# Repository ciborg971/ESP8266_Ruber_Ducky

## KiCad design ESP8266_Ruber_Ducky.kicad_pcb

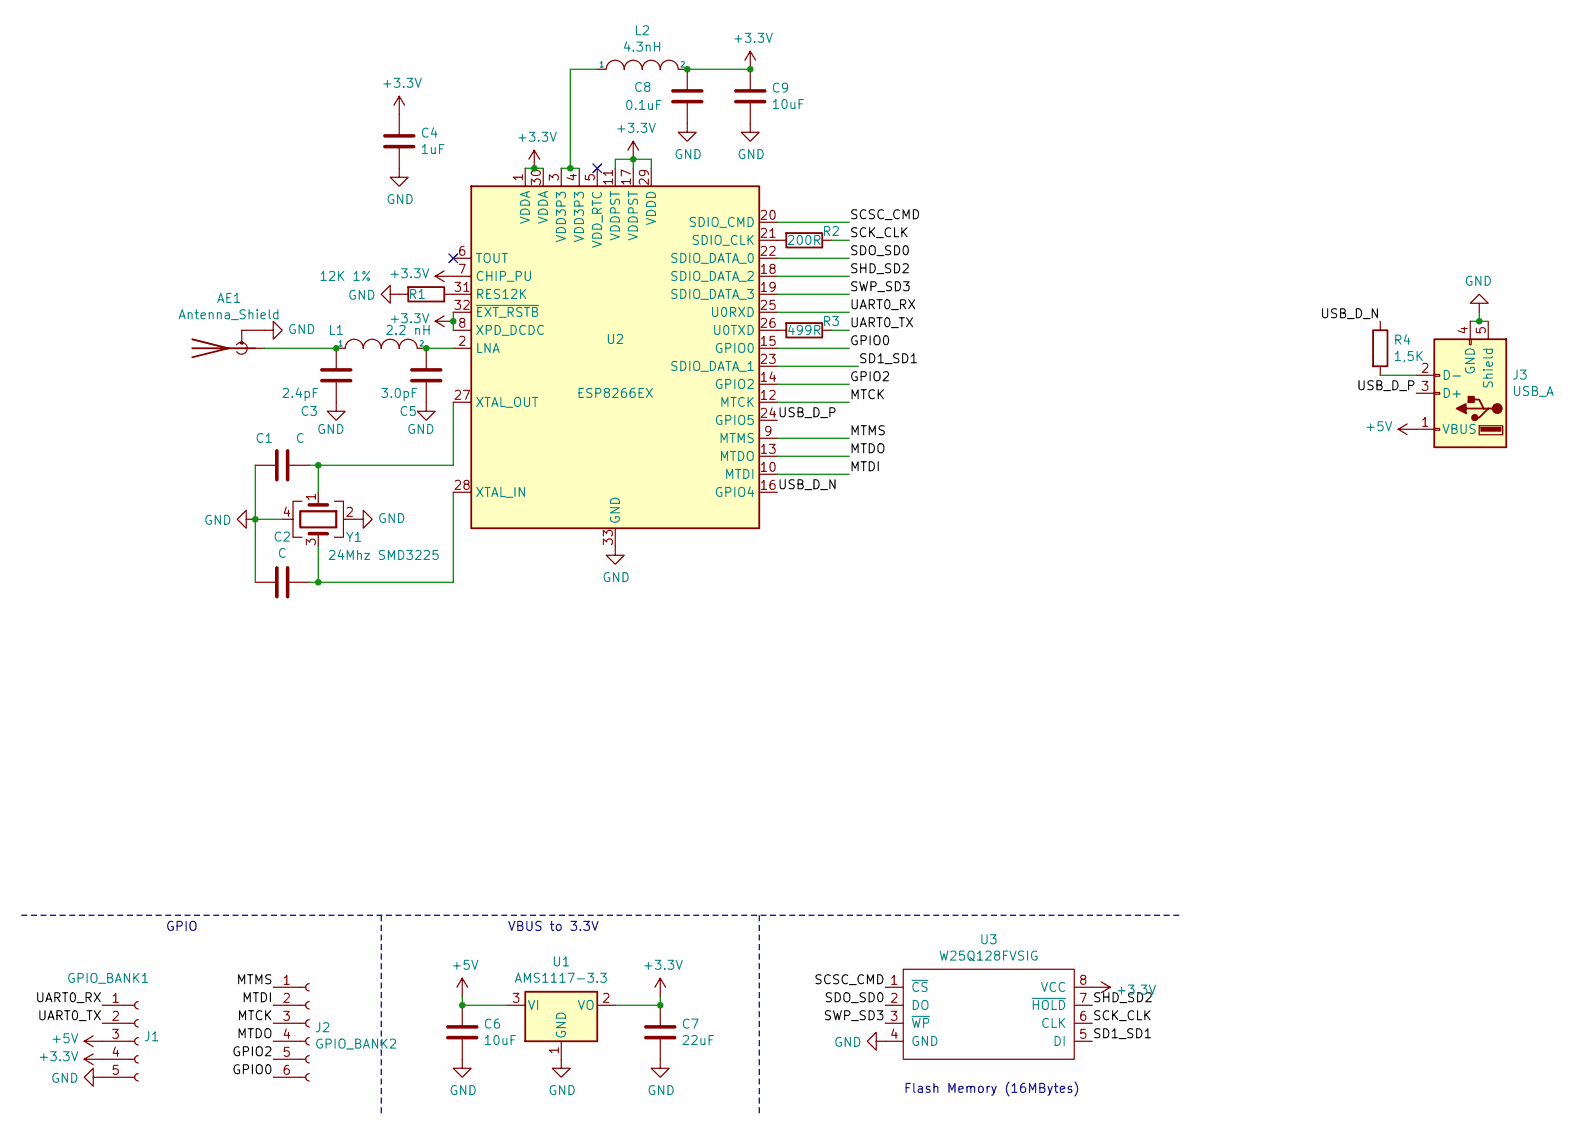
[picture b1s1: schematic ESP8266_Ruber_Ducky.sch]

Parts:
AE1: Antenna_Shield; SOIC-2
C1, C2: C; C_0201_0603Metric
C3: 2.4pF; C_0201_0603Metric
C4: 1uF; C_0201_0603Metric
C5: 3.0pF; C_0201_0603Metric
C6, C9: 10uF; C_0201_0603Metric
C7: 22uF; C_0201_0603Metric
C8: 0.1uF; C_0201_0603Metric
J1: GPIO_BANK1; PinHeader_1x05_P1.00mm_Vertical
J2: GPIO_BANK2; PinHeader_1x06_P1.00mm_Vertical
J3: USB_A; USB-A-PCB
L1: 2.2 nH; L_0201_0603Metric
L2: 4.3nH; L_0201_0603Metric
R1: 12K 1%; R_0201_0603Metric
R2: 200R; R_0201_0603Metric
R3: 499R; R_0201_0603Metric
R4: 1,5K; R_0201_0603Metric
U1: AMS1117-3.3; SOT-223-3_TabPin2
U2: ESP8266EX; QFN-32-1EP_5x5mm_P0.5mm_EP3.45x3.45mm
U3: W25Q128FVSIG; SOIC127P790X216-8N
Y1: 24Mhz SMD3225; Crystal_SMD_3225-4Pin_3.2x2.5mm

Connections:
+3V3: C4.1, C7.1, C8.1, C9.1, J1.4, L2.2, U1.2 (VO), U2.1 (VDDA), U2.7 (CHIP_PU), U2.8 (XPD_DCDC), U2.11 (VDDPST), U2.17 (VDDPST), U2.29 (VDDD), U2.30 (VDDA), U2.32 (~EXT_RSTB~), U3.8 (VCC)
+5V: C6.1, J1.3, J3.1 (VBUS), U1.3 (VI)
/GPIO0: J2.6, U2.15 (GPIO0)
/GPIO2: J2.5, U2.14 (GPIO2)
/MTCK: J2.3, U2.12 (MTCK)
/MTDI: J2.2, U2.10 (MTDI)
/MTDO: J2.4, U2.13 (MTDO)
/MTMS: J2.1, U2.9 (MTMS)
/SCK_CLK: R2.1, U3.6 (CLK)
/SCSC_CMD: U2.20 (SDIO_CMD), U3.1 (~CS)
/SD1_SD1: U2.23 (SDIO_DATA_1), U3.5 (DI)
/SDO_SD0: U2.22 (SDIO_DATA_0), U3.2 (DO)
/SHD_SD2: U2.18 (SDIO_DATA_2), U3.7 (~HOLD)
/SWP_SD3: U2.19 (SDIO_DATA_3), U3.3 (~WP)
/UART0_RX: J1.1, U2.25 (U0RXD)
/UART0_TX: J1.2, R3.1
/USB_D_N: R4.1, U2.16 (GPIO4)
/USB_D_P: J3.3 (D+), U2.24 (GPIO5)
GND: AE1.2 (Shield), C1.2, C2.2, C3.2, C4.2, C5.2, C6.2, C7.2, C8.2, C9.2, J1.5, J3.4 (GND), J3.5 (Shield), R1.2, U1.1 (GND), U2.33 (GND), U3.4 (GND), Y1.2, Y1.4
unnamed: AE1.1 (A), C3.1, L1.1
unnamed: C1.1, U2.27 (XTAL_OUT), Y1.1
unnamed: C2.1, U2.28 (XTAL_IN), Y1.3
unnamed: C5.1, L1.2, U2.2 (LNA)
unnamed: J3.2 (D-), R4.2
unnamed: L2.1, U2.3 (VDD3P3), U2.4 (VDD3P3)
unnamed: R1.1, U2.31 (RES12K)
unnamed: R2.2, U2.21 (SDIO_CLK)
unnamed: R3.2, U2.26 (U0TXD)

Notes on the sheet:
Flash Memory (16MBytes)
VBUS to 3.3V
GPIO

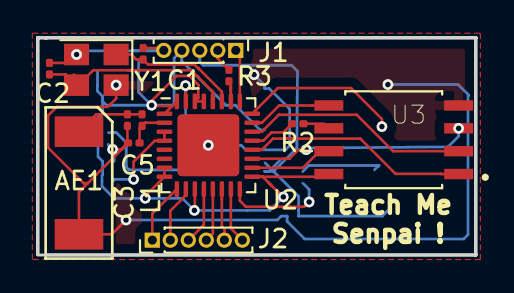
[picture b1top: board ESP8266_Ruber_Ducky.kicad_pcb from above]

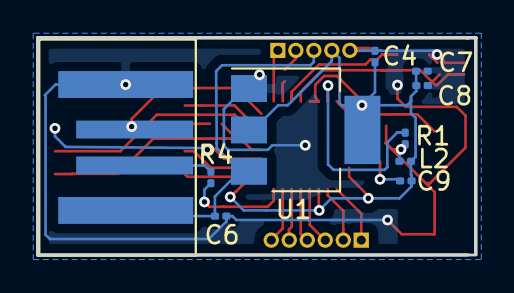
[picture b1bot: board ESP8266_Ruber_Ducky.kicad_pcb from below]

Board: 2 copper layers, 24.3 x 12.1 mm, 23 parts (10 on the bottom side), 28 nets.
